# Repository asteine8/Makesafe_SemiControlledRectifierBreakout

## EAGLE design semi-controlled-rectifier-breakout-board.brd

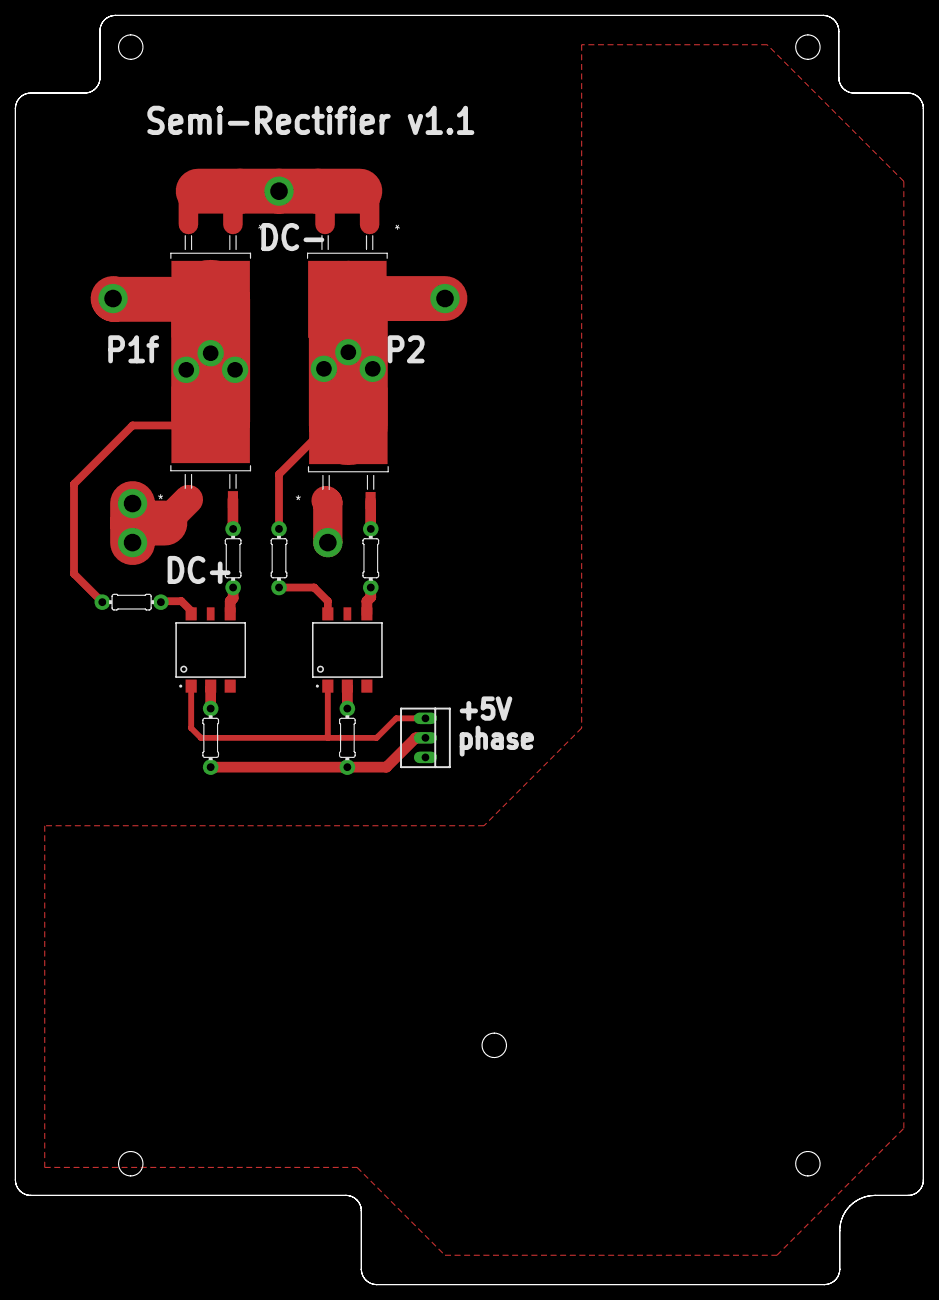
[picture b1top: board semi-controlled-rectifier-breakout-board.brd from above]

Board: 2 copper layers, 118.1 x 165.1 mm, 18 parts (0 on the bottom side), 15 nets.

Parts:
D1, D2: DIODE; 0204/7_TH
D8, D9: RFN20NS6SFHTL; DIO_RFN10N_ROM-M
R6A, R6B: 180; 0204/7_TH
R20A, R20B: 200; 0204/7_TH
U8, U9: TN4015H-6G; DIO_RFN10N_ROM-M
U10, U11: VO3053-X007T; SOIC254P1030X460-6N
U$1, U$2, U$3, U$4: 90MIL_TERMINAL
U$5: 1000MIL_JUMPER
X1: 22-23-2031

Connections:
+5VDC: U10.1, U11.1, X1.1
DC+: U8.1, U$3.1, U$5.2
DC-: D8.1, D8.2, D9.1, D9.2, U$4.1
unnamed: U9.1, U$5.1
unnamed: R6A.P$2, U10.4
unnamed: D1.P$2, U11.6
unnamed: R6B.P$2, U11.4
unnamed: R6A.P$1, U8.2
unnamed: R6B.P$1, U9.2
unnamed: R20A.P$2, U11.2
unnamed: R20B.P$2, U10.2
unnamed: D2.P$2, U10.6
P1_FUSED: D2.P$1, D8.3, U8.3, U$1.1
P2_IN: D1.P$1, D9.3, U9.3, U$2.1
PHASE_CONTROL_SIGNAL: R20A.P$1, R20B.P$1, X1.2

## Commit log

2022-03-10 Modified copper cut depth to cut all the way through the copper
2022-03-11 Modified flatcam files and brd layout
2022-03-11 Created new cam file, started new flatcam project, and added silkscreen layer for labeling
2022-03-11 exported and added tool database to repo
2022-03-11 Modified camfile and did isolation routing and silkscreen cutout in flatcam
2022-03-11 Fixed a trace on the brd model and generated images of flatcam and eagle projects
2022-03-21 Added board and via dimensions for new 2oz board
2022-03-21 Added 1mm milling bit to tools database file
2022-03-23 Increased P1,P2 trace width on board and added thermal vias. Exported CAM file and worked on flatcam project
2022-03-25 Added extra vias and updated flatcam project
2022-03-25 Added gcode files archive for 2 sided pcb
2022-03-26 Updated Copper cut depth for flatcam
2022-03-31 Added arduino pulse generator program for testing
2022-04-01 Added new board design for thermal rework
2022-04-02 Style changes to rectifier parts
2022-04-03 Updated cam job file
2022-04-03 Generated flatcam files for 2 sided pcb with thermal vias. Exported as gcode

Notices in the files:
parts and their libraries:
COPYRIGHT: Copyright (C) 2022 Ultra Librarian. All rights reserved.
